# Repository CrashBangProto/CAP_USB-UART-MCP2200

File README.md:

#Toadstool-MCP2200

**Toadstool Cap - MCP2200 USB to UART**

The Toadstool family is made up of breadboard-friendly prototyping boards that house a microcontroller, and modules called *Caps* that connect using a standard header.  The prototyping board is analagous to an Arduino/Launchpad and the Cap analagous to a shield/boosterpack.

This repository contains the schematics for the **Toadstool-MCP2200 Cap**, a USB to UART module that connects to  Toadstool prototyping boards using the common header.  The Microchip MCP2200 chip does all the work.

The boards were layed out using [KiCad](http://www.kicad-pcb.org) - KiCad is open source and awesome.

There are a number of other CrashBangProto respositories containing the schematics for other Toadstool boards and Caps, as well as sample code to get you up and running.

Visit the [Toadstool Webpages](http://www.crash-bang.com/projects/toadstool/) for more information on the project.

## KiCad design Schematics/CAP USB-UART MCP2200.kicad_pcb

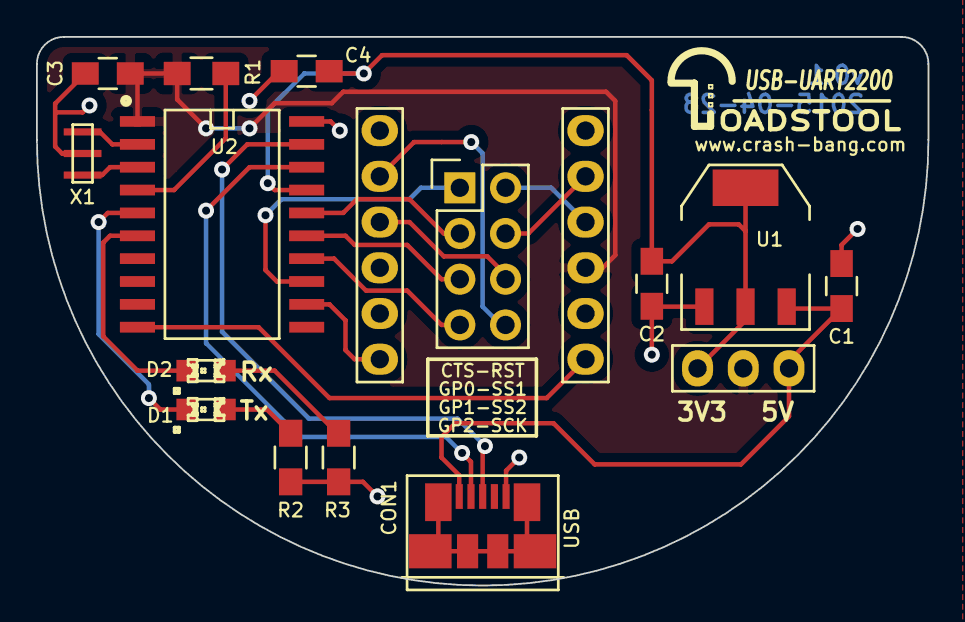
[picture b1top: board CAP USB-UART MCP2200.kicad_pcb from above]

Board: 2 copper layers, 49.5 x 30.5 mm, 18 parts (0 on the bottom side), 23 nets.

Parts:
C1: 100nF; C_0805_HandSoldering
C2: 10uF; C_0805_HandSoldering
C3, C4: 0.1uF; C_0805_HandSoldering
CON1: USB-MICRO-B; USB_Micro_B-Molex_47346-0001
D1: Tx; LED-0805
D2: Rx; LED-0805
K1: CAP_CONN_LHS; Socket_Strip_Stackable_1x06
K2: CAP_CONN_RHS; Socket_Strip_Stackable_1x06
K3: V_SELECT; Pin_Header_Straight_1x03
K4: GPIO_Connect; Pin_Header_Straight_2x04
R1: 10k; R_0805_HandSoldering
R2, R3: R; R_0805_HandSoldering
Toadstool_Logo: LOGO**; Toadstool_Logo
U1: LD1117S33TR; SOT-223
U2: MCP2200; SOIC-W-20
X1: 12MHz; CAP_CHIP_3.2x1.3

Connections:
+3V3: C2.1, C4.1, K3.3, U1.2, U2.17
+5V: C1.1, CON1.1, K3.1, U1.3
/CTS: K4.1, U2.13
/GP0: K4.3, U2.16
/GP1: K4.5, U2.15
/GP2: K4.7, U2.14
/RST: K2.3, K4.2
/RXD: K2.6, U2.10
/SCK: K1.2, K4.8
/SS1: K2.2, K4.4
/SS2: K1.3, K4.6
/TXD: K1.6, U2.12
GND: C1.2, C2.2, C3.1, C4.2, CON1.5, K1.4, R2.2, R3.2, U1.1, U2.20, X1.2
unnamed: CON1.2, U2.18
unnamed: CON1.3, U2.19
unnamed: D1.1, U2.5
unnamed: D1.2, R2.1
unnamed: D2.1, U2.6
unnamed: D2.2, R3.1
unnamed: R1.2, U2.4
unnamed: U2.2, X1.1
unnamed: U2.3, X1.3
VCC: C3.2, K2.4, K3.2, R1.1, U2.1

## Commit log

2015-05-15 :boom::camel: Added .gitattributes
